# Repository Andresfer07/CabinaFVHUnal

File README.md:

# CabinaFVHUnal

## 1. Descripción

Este repositorio contiene los archivos, diseños, datos y software desarrollados durante el proyecto **"Diseño e implementación de una cabina prototipo automatizada de bajo costo para la producción de Forraje Verde Hidropónico (FVH)"**.

El proyecto comprende el diseño y construcción de la cabina prototipo, los sistemas electrónicos y de control, el software de automatización, la interfaz de supervisión, AGRO-BOT, los diseños tridimensionales, los diseños de PCB, los datos de los ciclos de cultivo y el registro fotográfico del desarrollo del proyecto.

## 2. Recursos del proyecto

- **Video de funcionamiento:** [Ver video en YouTube](https://www.youtube.com/playlist?list=PLa2235HGgJpQ)
- **Dashboard remoto:** [Acceder al dashboard](https://cabinafvh.duckdns.org/dashboard/page1)
- **Repositorio complementario:** [Consultar archivos en Google Drive](https://drive.google.com/drive/folders/1n4Momb2bnFOUJLxZTVhM5PK6ztII8chc?usp=drive_link)

## 3. Organización del repositorio

La información se encuentra organizada en las siguientes carpetas:

- **Data Ciclos Cultivo:** datos registrados durante los ciclos experimentales, registros diarios y scripts de procesamiento y auditoría. Los archivos CSV consolidados de gran tamaño se conservan en Google Drive.
- **Diseños 3D:** modelos tridimensionales de la cabina, sus sistemas y componentes individuales. Los archivos F3D y STEP se conservan en Google Drive debido a su tamaño y características como archivos de diseño.
- **Interfaz Node-RED y AGRO-BOT:** archivos JSON correspondientes a los flujos de Node-RED y AGRO-BOT.
- **KiCad PCB:** proyectos de KiCad correspondientes a las PCB principal, de potencia y de sensores.
- **Python - Scripts de Control:** software de control ejecutado en la Raspberry Pi y archivos de datos utilizados por el sistema.
- **Registro Fotográfico:** registro visual de la construcción de la cabina y de los ciclos de cultivo. Las fotografías se conservan en el repositorio complementario de Google Drive debido a su tamaño.

Cada carpeta contiene un README específico con información sobre su contenido y organización.

## 4. Plataforma de control

El sistema de control fue implementado sobre una **Raspberry Pi 3B+**, utilizando Python como base para la ejecución de las funciones de automatización y control.

La arquitectura desarrollada también integra herramientas como Node-RED, Mosquitto e InfluxDB para las funciones de supervisión, comunicación y almacenamiento de información.

## 5. Reproducción de los archivos

Los archivos proporcionados permiten consultar y reproducir los diferentes desarrollos realizados durante el proyecto.

### Software de control

La estructura de la carpeta `Python - Scripts de Control` debe conservarse para mantener correctamente las relaciones entre el archivo principal y los módulos utilizados.

El archivo principal es:

```text
main2.py
```

Para ejecutar el sistema de control en la Raspberry Pi:

```bash
sudo python3 main2.py
```

Las dependencias de Python requeridas se encuentran especificadas en el archivo `requirements.txt` de la carpeta `Python - Scripts de Control`.

El uso de `sudo` es necesario debido a los requerimientos de acceso al hardware utilizados para el control de la iluminación mediante LEDs WS2812B.

### Flujos de Node-RED

Los flujos de Node-RED pueden reproducirse mediante la opción de **Importar** de Node-RED a partir de los archivos JSON proporcionados en `Interfaz Node-RED y AGRO-BOT`.

Los nodos de MQTT e InfluxDB requieren ajustar la dirección del broker y la base de datos según el entorno de ejecución (ver README de la carpeta `Interfaz Node-RED y AGRO-BOT`).

### Diseños 3D

Los modelos tridimensionales desarrollados durante el proyecto se encuentran disponibles en el repositorio complementario de Google Drive, cuyo enlace se encuentra en la sección **Recursos del proyecto**.

Los archivos F3D pueden abrirse y editarse mediante Autodesk Fusion 360. Los archivos STEP permiten la visualización e interoperabilidad de los modelos con otros programas de diseño asistido por computador.

### Diseños PCB

Los proyectos contenidos en `KiCad PCB` pueden abrirse mediante KiCad conservando los archivos propios de cada proyecto.

### Datos experimentales

Los archivos de `Data Ciclos Cultivo` contienen los registros diarios originales y los scripts utilizados para su procesamiento y auditoría.

Los archivos CSV consolidados de gran tamaño se conservan en el repositorio complementario de Google Drive, cuyo enlace se encuentra en la sección **Recursos del proyecto**.

### Registro Fotográfico

El registro fotográfico de la construcción de la cabina y de los ciclos de cultivo se encuentra disponible en el repositorio complementario de Google Drive, cuyo enlace se encuentra en la sección **Recursos del proyecto**.

## 6. Datos y documentación

Los datos, diseños y archivos de software contenidos en este repositorio corresponden a los desarrollos realizados durante el proyecto y constituyen el soporte técnico y experimental de la tesis.

La documentación se complementa con el documento de tesis, donde se presentan el diseño, implementación, metodología, validación y resultados obtenidos.

## 7. Requisitos generales

La reproducción completa del sistema físico requiere la plataforma de hardware y los componentes utilizados durante el desarrollo del prototipo.

Para la reproducción de los archivos digitales se requieren las herramientas correspondientes a cada tipo de recurso, entre ellas:

- Raspberry Pi OS y Python para el software de control.
- Node-RED para los flujos de supervisión y control.
- Mosquitto (broker MQTT) e InfluxDB para la comunicación y el almacenamiento de datos.
- KiCad para los diseños de PCB.
- Autodesk Fusion 360 u otro software compatible para los modelos 3D.
- Herramientas compatibles con archivos CSV y JSON para la consulta de datos.

## 8. Alcance

Este repositorio tiene como finalidad conservar y facilitar la consulta, trazabilidad y reproducción de los principales recursos desarrollados durante el proyecto de la cabina prototipo automatizada para producción de FVH.

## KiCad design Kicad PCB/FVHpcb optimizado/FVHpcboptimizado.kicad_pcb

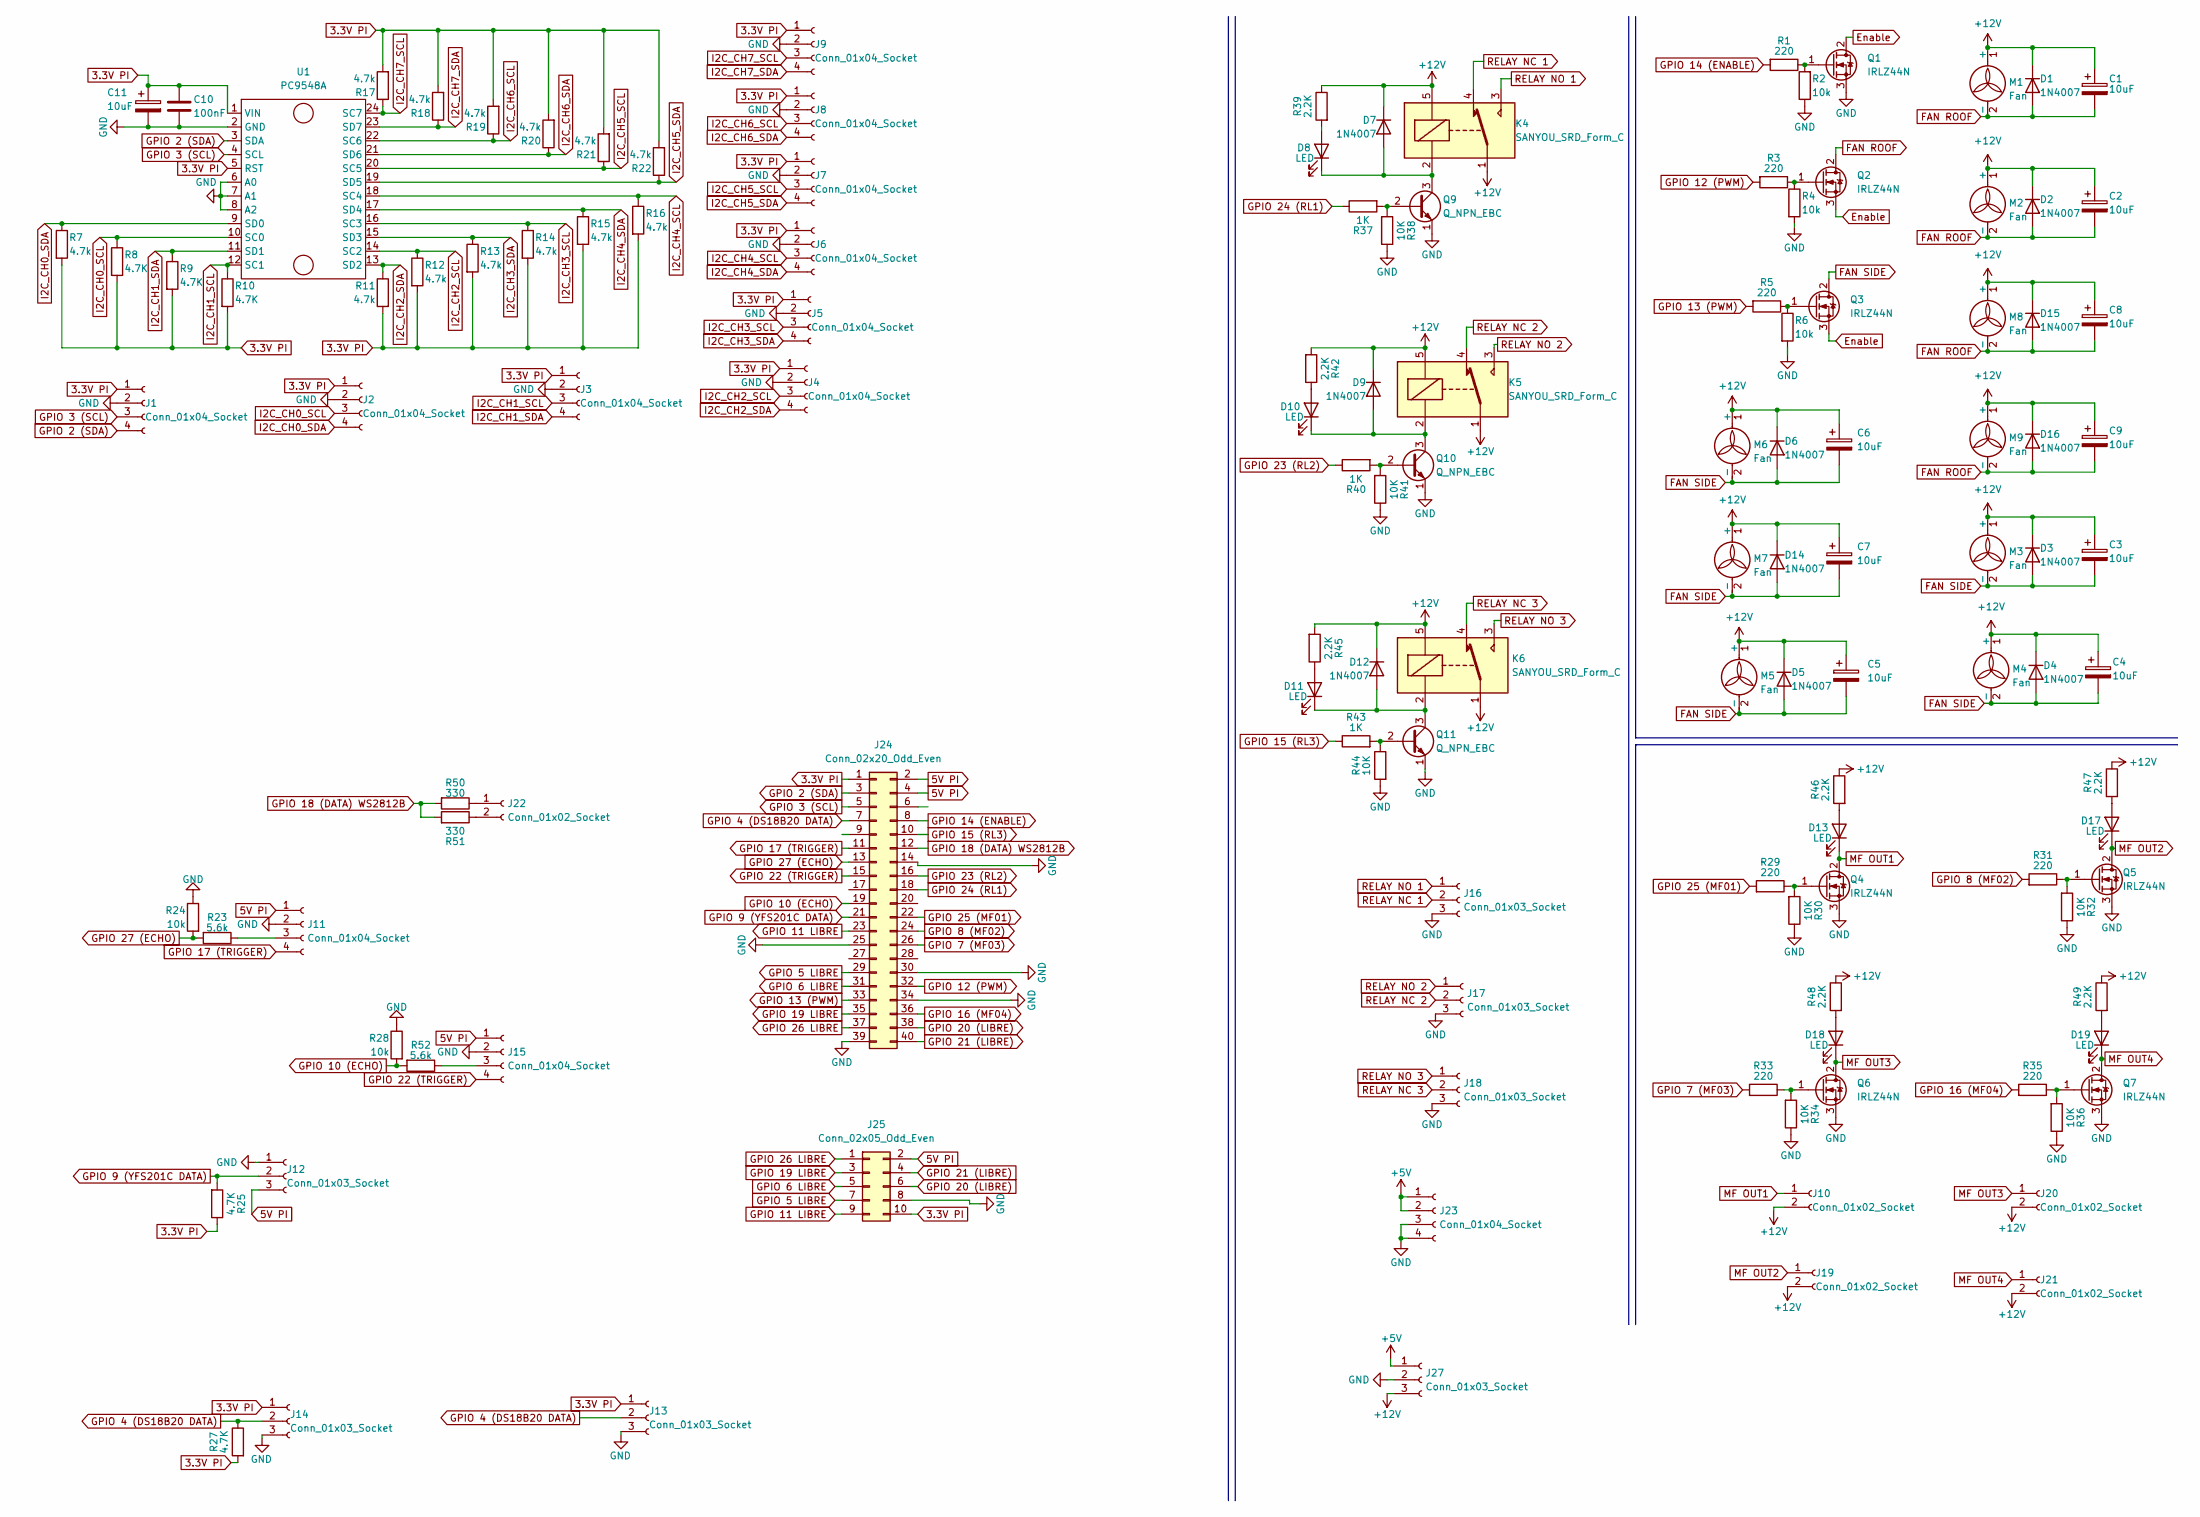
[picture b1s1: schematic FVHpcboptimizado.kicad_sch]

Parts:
C1, C2, C3, C4, C5, C6, C7, C8, C9, C11: 10uF; CP_Radial_D5.0mm_P2.00mm
C10: 100nF; C_Disc_D5.0mm_W2.5mm_P5.00mm
D1, D2, D3, D4, D5, D6, D7, D9, D12, D14, D15, D16: 1N4007; D_DO-41_SOD81_P10.16mm_Horizontal
D8, D10, D11, D13, D17, D18, D19: LED; LED_D3.0mm
J1, J2, J3, J4, J5, J6, J7, J8, J9, J11, J15: Conn_01x04_Socket; JST_XH_B4B-XH-A_1x04_P2.50mm_Vertical
J10, J19, J20, J21: Conn_01x02_Socket; TerminalBlock_Phoenix_MKDS-1,5-2_1x02_P5.00mm_Horizontal
J12, J13, J14: Conn_01x03_Socket; JST_XH_B3B-XH-A_1x03_P2.50mm_Vertical
J16, J17, J18: Conn_01x03_Socket; TerminalBlock_Phoenix_MKDS-1,5-3_1x03_P5.00mm_Horizontal
J22: Conn_01x02_Socket; TerminalBlock_Ningbo-Kagnex_HB9500M_1x02_P9.5mm
J23: Conn_01x04_Socket; TerminalBlock_Ningbo-Kagnex_HB9500M_1x04_P9.5mm
J24: Conn_02x20_Odd_Even; IDC-Header_2x20_P2.54mm_Vertical
J25: Conn_02x05_Odd_Even; PinHeader_2x05_P2.54mm_Vertical
J27: Conn_01x03_Socket; TerminalBlock_Ningbo-Kagnex_HB9500M_1x03_P9.5mm
K4, K5, K6: SANYOU_SRD_Form_C; Relay_SPDT_SANYOU_SRD_Series_Form_C
M1, M2, M3, M4, M5, M6, M7, M8, M9: Fan; Molex_KK-254_AE-6410-02A_1x02_P2.54mm_Vertical
Q1, Q2, Q3, Q4, Q5, Q6, Q7: IRLZ44N; TO-220-3_Vertical
Q9, Q10, Q11: Q_NPN_EBC; TO-92_Inline
R1, R3, R5, R29, R31, R33, R35: 220; R_Axial_DIN0207_L6.3mm_D2.5mm_P10.16mm_Horizontal
R2, R4, R6, R24, R28: 10k; R_Axial_DIN0207_L6.3mm_D2.5mm_P10.16mm_Horizontal
R7, R11, R12, R13, R14, R15, R16, R17, R18, R19, R20, R21, R22: 4.7k; R_Axial_DIN0207_L6.3mm_D2.5mm_P10.16mm_Horizontal
R8, R9, R10, R25, R27: 4.7K; R_Axial_DIN0207_L6.3mm_D2.5mm_P10.16mm_Horizontal
R23, R52: 5.6k; R_Axial_DIN0207_L6.3mm_D2.5mm_P10.16mm_Horizontal
R30, R32, R34, R36, R38, R41, R44: 10K; R_Axial_DIN0207_L6.3mm_D2.5mm_P10.16mm_Horizontal
R37, R40, R43: 1K; R_Axial_DIN0207_L6.3mm_D2.5mm_P10.16mm_Horizontal
R39, R42, R45, R46, R47, R48, R49: 2.2K; R_Axial_DIN0207_L6.3mm_D2.5mm_P10.16mm_Horizontal
R50, R51: 330; R_Axial_DIN0207_L6.3mm_D2.5mm_P10.16mm_Horizontal
U1: PC9548A; PC9548A_Morado

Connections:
3.3V PI: C10.1, C11.1, J1.1, J2.1, J3.1, J4.1, J5.1, J6.1, J7.1, J8.1, J9.1, J13.1, J14.1, J24.1, J25.10, R7.2, R8.2, R9.2, R10.2, R11.2, R12.2, R13.2, R14.2, R15.2, R16.2, R17.2, R18.2, R19.2, R20.2, R21.2, R22.2, R25.1, R27.2, U1.1 (VIN), U1.5 (RST)
5V PI: J11.1, J12.3, J15.1, J24.2, J24.4, J25.2
+5V: J23.1, J23.2, J27.1
+12V: C1.1, C2.1, C3.1, C4.1, C5.1, C6.1, C7.1, C8.1, C9.1, D1.1 (K), D2.1 (K), D3.1 (K), D4.1 (K), D5.1 (K), D6.1 (K), D7.1 (K), D9.1 (K), D12.1 (K), D14.1 (K), D15.1 (K), D16.1 (K), J10.2, J19.2, J20.2, J21.2, J27.3, K4.1, K4.5, K5.1, K5.5, K6.1, K6.5, M1.1 (+), M2.1 (+), M3.1 (+), M4.1 (+), M5.1 (+), M6.1 (+), M7.1 (+), M8.1 (+), M9.1 (+), R39.1, R42.2, R45.2, R46.1, R47.1, R48.1, R49.1
Enable: Q1.2 (D), Q2.3 (S), Q3.3 (S)
FAN ROOF: C1.2, C2.2, C8.2, C9.2, D1.2 (A), D2.2 (A), D15.2 (A), D16.2 (A), M1.2 (-), M2.2 (-), M8.2 (-), M9.2 (-), Q2.2 (D)
FAN SIDE: C3.2, C4.2, C5.2, C6.2, C7.2, D3.2 (A), D4.2 (A), D5.2 (A), D6.2 (A), D14.2 (A), M3.2 (-), M4.2 (-), M5.2 (-), M6.2 (-), M7.2 (-), Q3.2 (D)
GND: C10.2, C11.2, J1.2, J2.2, J3.2, J4.2, J5.2, J6.2, J7.2, J8.2, J9.2, J11.2, J12.1, J13.3, J14.3, J15.2, J16.3, J17.3, J18.3, J23.3, J23.4, J24.14, J24.25, J24.30, J24.34, J24.39, J25.8, J27.2, Q1.3 (S), Q4.3 (S), Q5.3 (S), Q6.3 (S), Q7.3 (S), Q9.1 (E), Q10.1 (E), Q11.1 (E), R2.1, R4.2, R6.2, R24.1, R28.1, R30.1, R32.1, R34.1, R36.1, R38.1, R41.1, R44.2, U1.2 (GND), U1.6 (A0), U1.7 (A1), U1.8 (A2)
GPIO 2 (SDA): J1.4, J24.3, U1.3 (SDA)
GPIO 3 (SCL): J1.3, J24.5, U1.4 (SCL)
GPIO 4 (DS18B20 DATA): J13.2, J14.2, J24.7, R27.1
GPIO 5 LIBRE: J24.29, J25.7
GPIO 6 LIBRE: J24.31, J25.5
GPIO 7 (MF03): J24.26, R33.2
GPIO 8 (MF02): J24.24, R31.2
GPIO 9 (YFS201C DATA): J12.2, J24.21, R25.2
GPIO 10 (ECHO): J24.19, R28.2, R52.2
GPIO 11 LIBRE: J24.23, J25.9
GPIO 12 (PWM): J24.32, R3.2
GPIO 13 (PWM): J24.33, R5.2
GPIO 14 (ENABLE): J24.8, R1.2
GPIO 15 (RL3): J24.10, R43.1
GPIO 16 (MF04): J24.36, R35.2
GPIO 17 (TRIGGER): J11.4, J24.11
GPIO 18 (DATA) WS2812B: J24.12, R50.2, R51.2
GPIO 19 LIBRE: J24.35, J25.3
GPIO 20 (LIBRE): J24.38, J25.6
GPIO 21 (LIBRE): J24.40, J25.4
GPIO 22 (TRIGGER): J15.4, J24.15
GPIO 23 (RL2): J24.16, R40.1
GPIO 24 (RL1): J24.18, R37.1
GPIO 25 (MF01): J24.22, R29.2
GPIO 26 LIBRE: J24.37, J25.1
GPIO 27 (ECHO): J24.13, R23.2, R24.2
I2C_CH0_SCL: J2.3, R8.1, U1.10 (SC0)
I2C_CH0_SDA: J2.4, R7.1, U1.9 (SD0)
I2C_CH1_SCL: J3.3, R10.1, U1.12 (SC1)
I2C_CH1_SDA: J3.4, R9.1, U1.11 (SD1)
I2C_CH2_SCL: J4.3, R12.1, U1.14 (SC2)
I2C_CH2_SDA: J4.4, R11.1, U1.13 (SD2)
I2C_CH3_SCL: J5.3, R14.1, U1.16 (SC3)
I2C_CH3_SDA: J5.4, R13.1, U1.15 (SD3)
I2C_CH4_SCL: J6.3, R16.1, U1.18 (SC4)
I2C_CH4_SDA: J6.4, R15.1, U1.17 (SD4)
I2C_CH5_SCL: J7.3, R21.1, U1.20 (SC5)
I2C_CH5_SDA: J7.4, R22.1, U1.19 (SD5)
I2C_CH6_SCL: J8.3, R19.1, U1.22 (SC6)
I2C_CH6_SDA: J8.4, R20.1, U1.21 (SD6)
I2C_CH7_SCL: J9.3, R17.1, U1.24 (SC7)
I2C_CH7_SDA: J9.4, R18.1, U1.23 (SD7)
MF OUT1: D13.1 (K), J10.1, Q4.2 (D)
MF OUT2: D17.1 (K), J19.1, Q5.2 (D)
MF OUT3: D18.1 (K), J20.1, Q6.2 (D)
MF OUT4: D19.1 (K), J21.1, Q7.2 (D)
unnamed: D7.2 (A), D8.1 (K), K4.2, Q9.3 (C)
unnamed: D8.2 (A), R39.2
unnamed: D10.2 (A), R42.1
unnamed: D9.2 (A), D10.1 (K), K5.2, Q10.3 (C)
unnamed: D11.2 (A), R45.1
unnamed: D11.1 (K), D12.2 (A), K6.2, Q11.3 (C)
unnamed: D13.2 (A), R46.2
unnamed: D17.2 (A), R47.2
unnamed: D18.2 (A), R48.2
unnamed: D19.2 (A), R49.2
unnamed: J11.3, R23.1
unnamed: J15.3, R52.1
unnamed: J22.1, R50.1
unnamed: J22.2, R51.1
unnamed: Q1.1 (G), R1.1, R2.2
unnamed: Q2.1 (G), R3.1, R4.1
unnamed: Q3.1 (G), R5.1, R6.1
unnamed: Q4.1 (G), R29.1, R30.2
unnamed: Q5.1 (G), R31.1, R32.2
unnamed: Q6.1 (G), R33.1, R34.2
unnamed: Q7.1 (G), R35.1, R36.2
unnamed: Q9.2 (B), R37.2, R38.2
unnamed: Q10.2 (B), R40.2, R41.2
unnamed: Q11.2 (B), R43.2, R44.1
RELAY NC 1: J16.2, K4.4
RELAY NC 2: J17.2, K5.4
RELAY NC 3: J18.2, K6.4
RELAY NO 1: J16.1, K4.3
RELAY NO 2: J17.1, K5.3
RELAY NO 3: J18.1, K6.3

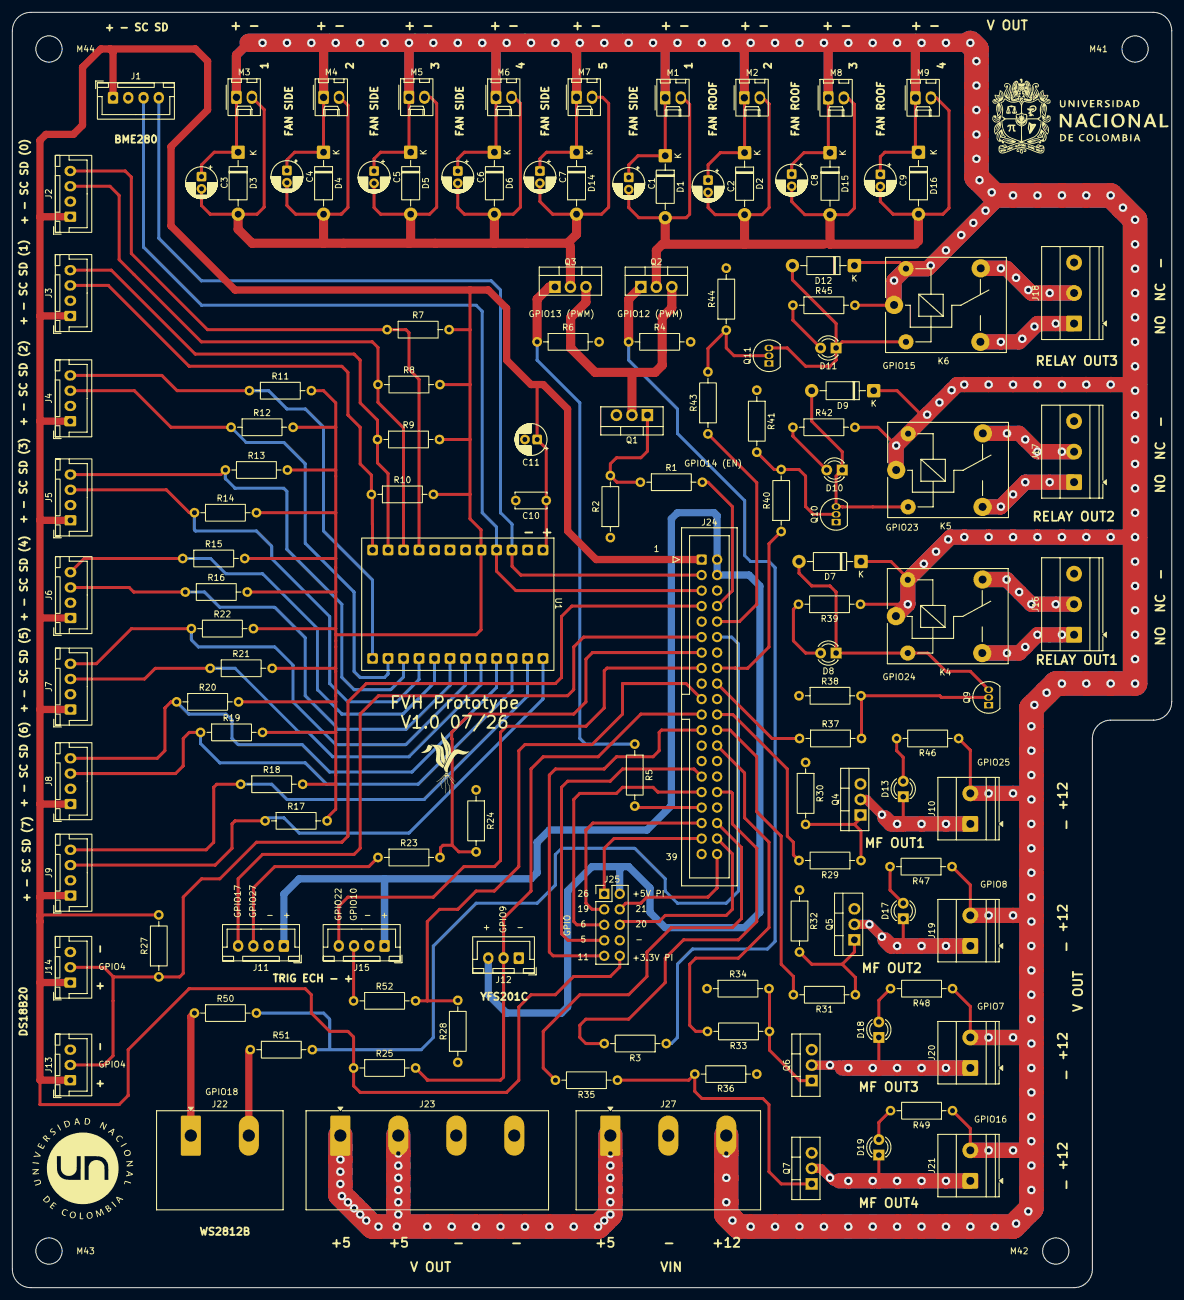
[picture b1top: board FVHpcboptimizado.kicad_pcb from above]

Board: 2 copper layers, 190.0 x 209.0 mm, 134 parts (0 on the bottom side), 84 nets.

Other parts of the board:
M41, M42, M43, M44: MountingHole_4.3mm_M4

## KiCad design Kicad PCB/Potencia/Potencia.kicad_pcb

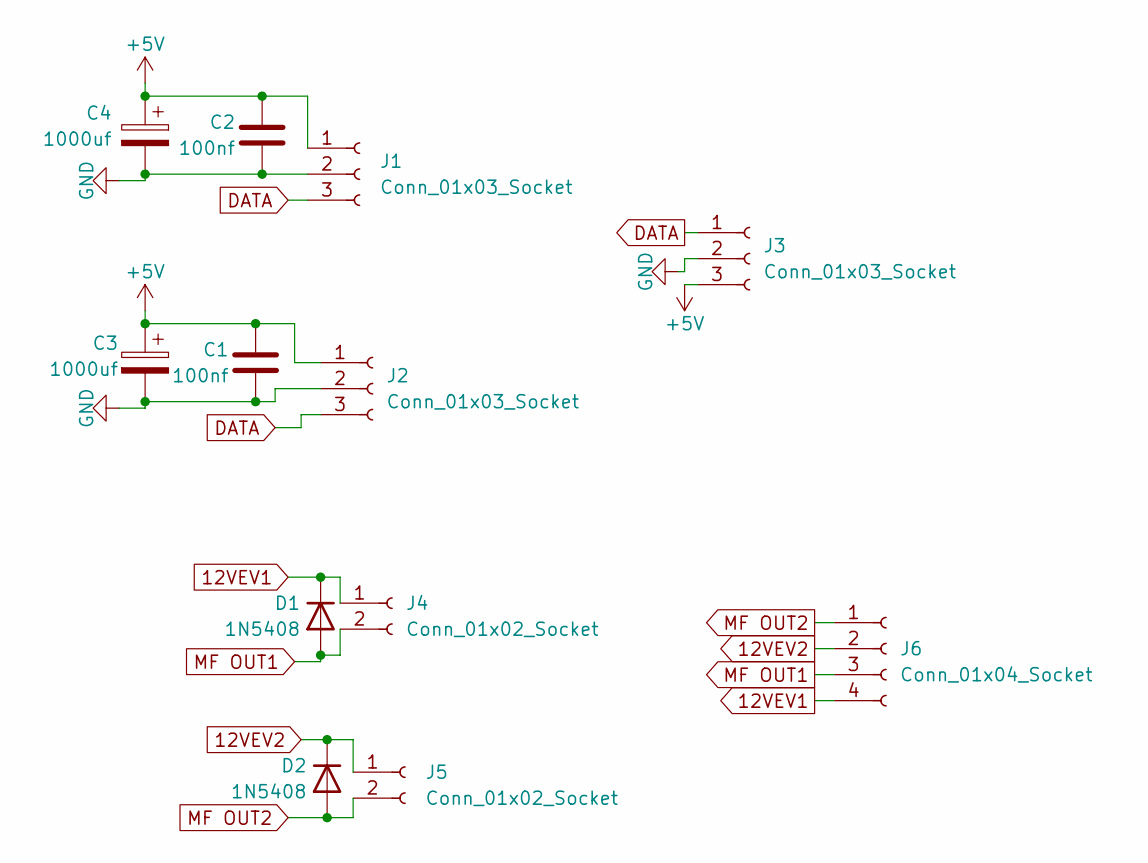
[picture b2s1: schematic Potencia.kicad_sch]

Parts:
C1, C2: 100nf; C_Disc_D5.0mm_W2.5mm_P2.50mm
C3, C4: 1000uf; CP_Radial_D13.0mm_P5.00mm
D1, D2: 1N5408; D_DO-201AD_P15.24mm_Horizontal
J1, J2: Conn_01x03_Socket; PhoenixContact_MSTBVA_2,5_3-G-5,08_1x03_P5.08mm_Vertical
J3: Conn_01x03_Socket; PhoenixContact_GMSTBVA_2,5_3-G-7,62_1x03_P7.62mm_Vertical
J4, J5: Conn_01x02_Socket; PhoenixContact_MSTBVA_2,5_2-G-5,08_1x02_P5.08mm_Vertical
J6: Conn_01x04_Socket; PhoenixContact_GMSTBVA_2,5_4-G-7,62_1x04_P7.62mm_Vertical

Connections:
12VEV1: D1.1 (K), J4.1, J6.4
12VEV2: D2.1 (K), J5.1, J6.2
+5V: C1.1, C2.1, C3.1, C4.1, J1.1, J2.1, J3.3
DATA: J1.3, J2.3, J3.1
GND: C1.2, C2.2, C3.2, C4.2, J1.2, J2.2, J3.2
MF OUT1: D1.2 (A), J4.2, J6.3
MF OUT2: D2.2 (A), J5.2, J6.1

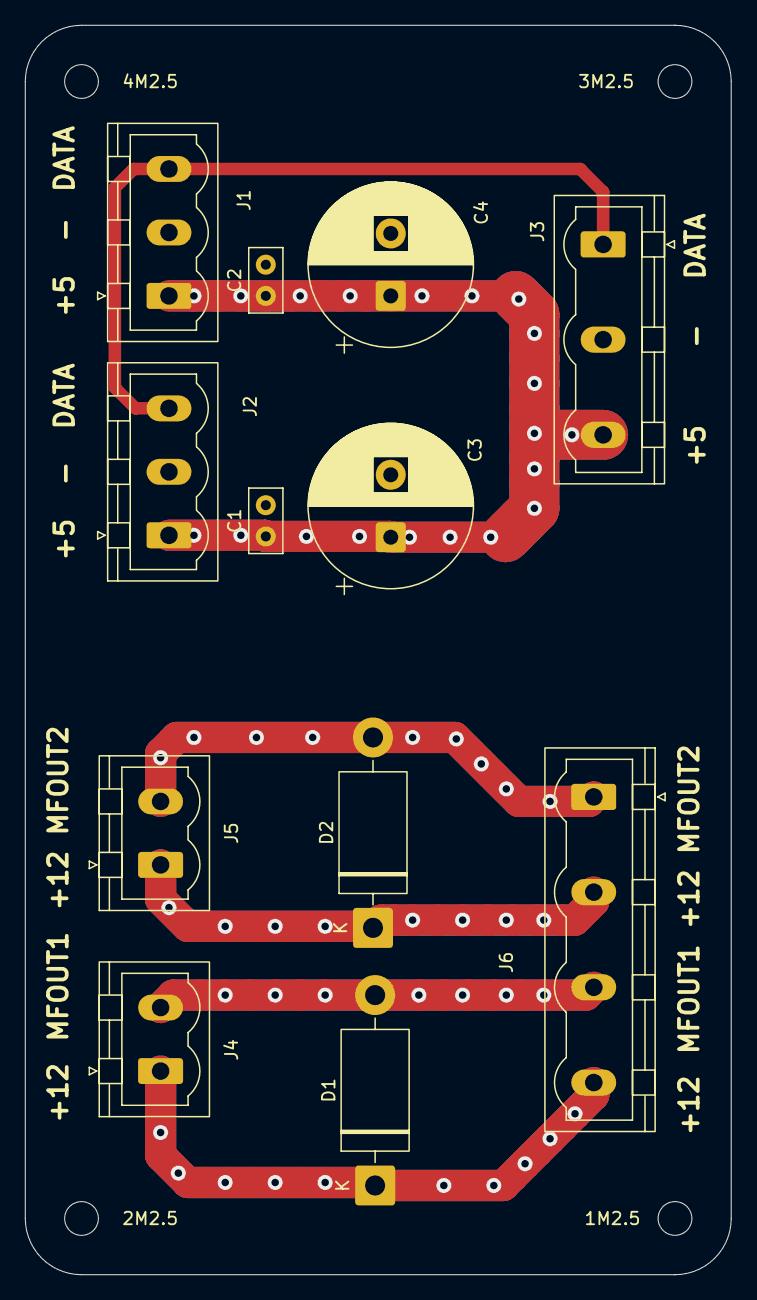
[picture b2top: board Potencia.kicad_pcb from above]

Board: 2 copper layers, 56.5 x 100.0 mm, 16 parts (0 on the bottom side), 7 nets.

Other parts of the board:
1M2.5, 2M2.5, 3M2.5, 4M2.5: MountingHole_2.7mm_M2.5
